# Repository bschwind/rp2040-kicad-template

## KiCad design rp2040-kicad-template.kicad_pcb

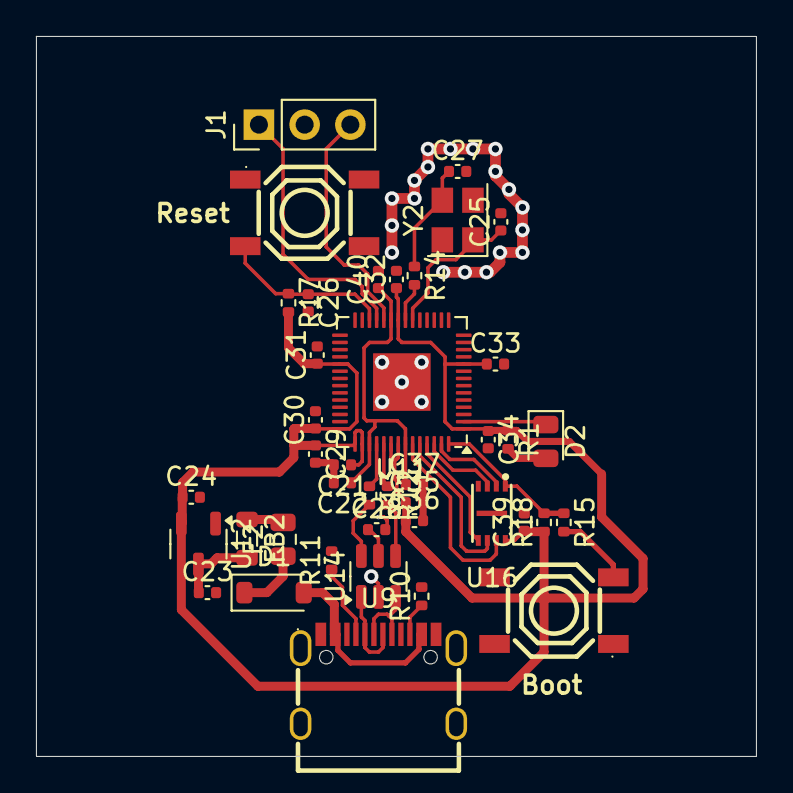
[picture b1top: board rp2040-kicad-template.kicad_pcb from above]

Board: 2 copper layers, 40.0 x 40.0 mm, 41 parts (0 on the bottom side), 28 nets.

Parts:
C21, C22, C39: 2.2uF; C_0402_1005Metric
C23, C24: 1uF; C_0402_1005Metric
C25, C27: 30pF; C_0402_1005Metric
C26, C28, C29, C30, C31, C32, C33, C34, C35, C36, C37, C40: 100nF; C_0402_1005Metric
D1: 5819W; D_SOD-123
D2: User LED (Blue); LED_0805_2012Metric
F2: TLC_PSMD050; Fuse_0805_2012Metric
FB2: 100@100MHz; L_0805_2012Metric
J1: Conn_01x03; PinHeader_1x03_P2.54mm_Vertical
R1, R14, R15: 1k ohm; R_0402_1005Metric
R10, R11: 5.1k; R_0402_1005Metric
R12, R13: 27 ohm; R_0402_1005Metric
R17, R18: 10k ohm; R_0402_1005Metric
U9: TYPE-C-31-M-12; simple-usb-c
U11: RP2040; QFN-56-1EP_7x7mm_P0.4mm_EP3.2x3.2mm
U12: XC6206PxxxMR; SOT-23-3
U13: USB Boot; tactile-switch
U14: USBLC6-2SC6; SOT-23-6
U15: Reset; tactile-switch
U16: W25Q16JVUXIQ; w25q16jvuxiq
Y2: 12MHz - 20pF; Crystal_SMD_3225-4Pin_3.2x2.5mm

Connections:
+1V1: C22.1, C37.1, C40.1, U11.23 (DVDD), U11.45 (VREG_VOUT), U11.50 (DVDD)
+3V3: C21.1, C24.1, C29.1, C30.1, C31.1, C32.1, C33.1, C34.1, C35.1, C36.1, C39.1, R1.1, R17.2, R18.1, U11.1 (IOVDD), U11.10 (IOVDD), U11.22 (IOVDD), U11.33 (IOVDD), U11.42 (IOVDD), U11.43 (ADC_AVDD), U11.44 (VREG_IN), U11.48 (USB_VDD), U11.49 (IOVDD), U12.2 (VO), U16.8 (VCC)
+5V: C23.1, FB2.2, U12.3 (VI)
/USER_LED: D2.1 (K), U11.2 (GPIO0)
/rp2040/CC1: R11.1, U9.A5 (CC1)
/rp2040/CC2: R10.1, U9.B5 (CC2)
/rp2040/OSC_IN: C27.1, R14.1, Y2.3
/rp2040/OSC_OUT: C25.1, U11.20 (XIN), Y2.1
/rp2040/QSPI_SD1: U11.55 (QSPI_SD1), U16.2 (DO(IO1))
/rp2040/QSPI_SD2: U11.54 (QSPI_SD2), U16.3 (WP#(IO2))
/rp2040/QSPI_SS: R15.1, R18.2, U11.56 (QSPI_SS), U16.1 (CS#)
/rp2040/RUN: C26.1, R17.1, U11.26 (RUN), U15.3 (C), U15.4 (D)
/rp2040/SWCLK: J1.3, U11.24 (SWCLK)
/rp2040/SWD: J1.1, U11.25 (SWD)
/rp2040/USB+: R12.2, U9.A6 (DP1), U9.B6 (DP2), U14.3 (I/O2), U14.4 (I/O2)
/rp2040/USB-: R13.2, U9.A7 (DN1), U9.B7 (DN2), U14.1 (I/O1), U14.6 (I/O1)
/rp2040/USB_MCU+: R12.1, U11.47 (USB_DP)
/rp2040/USB_MCU-: R13.1, U11.46 (USB_DM)
/rp2040/VBUS: C28.1, D1.2 (A), U9.A4 (VBUS), U9.A9 (VBUS), U9.B4 (VBUS), U9.B9 (VBUS), U14.5 (VBUS)
GND: C21.2, C22.2, C23.2, C24.2, C25.2, C26.2, C27.2, C28.2, C29.2, C30.2, C31.2, C32.2, C33.2, C34.2, C35.2, C36.2, C37.2, C39.2, C40.2, J1.2, R10.2, R11.2, U9.A1 (GND), U9.A12 (GND), U9.B1 (GND), U9.B12 (GND), U11.19 (TESTEN), U11.57 (GND), U12.1 (GND), U13.1 (A), U13.2 (B), U14.2 (GND), U15.1 (A), U15.2 (B), U16.4 (GND), Y2.2, Y2.4
unnamed: D1.1 (K), F2.1
unnamed: D2.2 (A), R1.2
unnamed: F2.2, FB2.1
unnamed: R15.2, U13.3 (C), U13.4 (D)
QSPI_SCLK: U11.52 (QSPI_SCLK), U16.6 (CLK)
QSPI_SD0: U11.53 (QSPI_SD0), U16.5 (DI(IO0))
QSPI_SD3: U11.51 (QSPI_SD3), U16.7 (HOLD#orRESET#(IO3))
XOUT_MCU: R14.2, U11.21 (XOUT)

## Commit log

2024-07-13 Add parts libraries
2024-07-13 Update some footprint references and use the newer footprint library
2024-07-13 Update parts libraries
2024-07-13 Schematic tweak
2024-07-28 Add a different ESD protection unit
2025-02-02 Move the RP2040 and associated components to a separate schematic sheet
2025-02-09 Update board design rules, use some smaller components, start laying out PCB
2025-02-24 Use more 0402 footprints for passive components
2025-09-20 Update to kicad 9
2025-09-21 Progress on the PCB layout
2025-09-21 Replace the SWD TRRS connector with a simple header pin connector
2025-10-11 Update design constraints
2025-10-11 Start some routing
2025-10-19 More routing
2025-10-19 Add some preset via sizes
2025-11-08 Adjust a few more tracks
